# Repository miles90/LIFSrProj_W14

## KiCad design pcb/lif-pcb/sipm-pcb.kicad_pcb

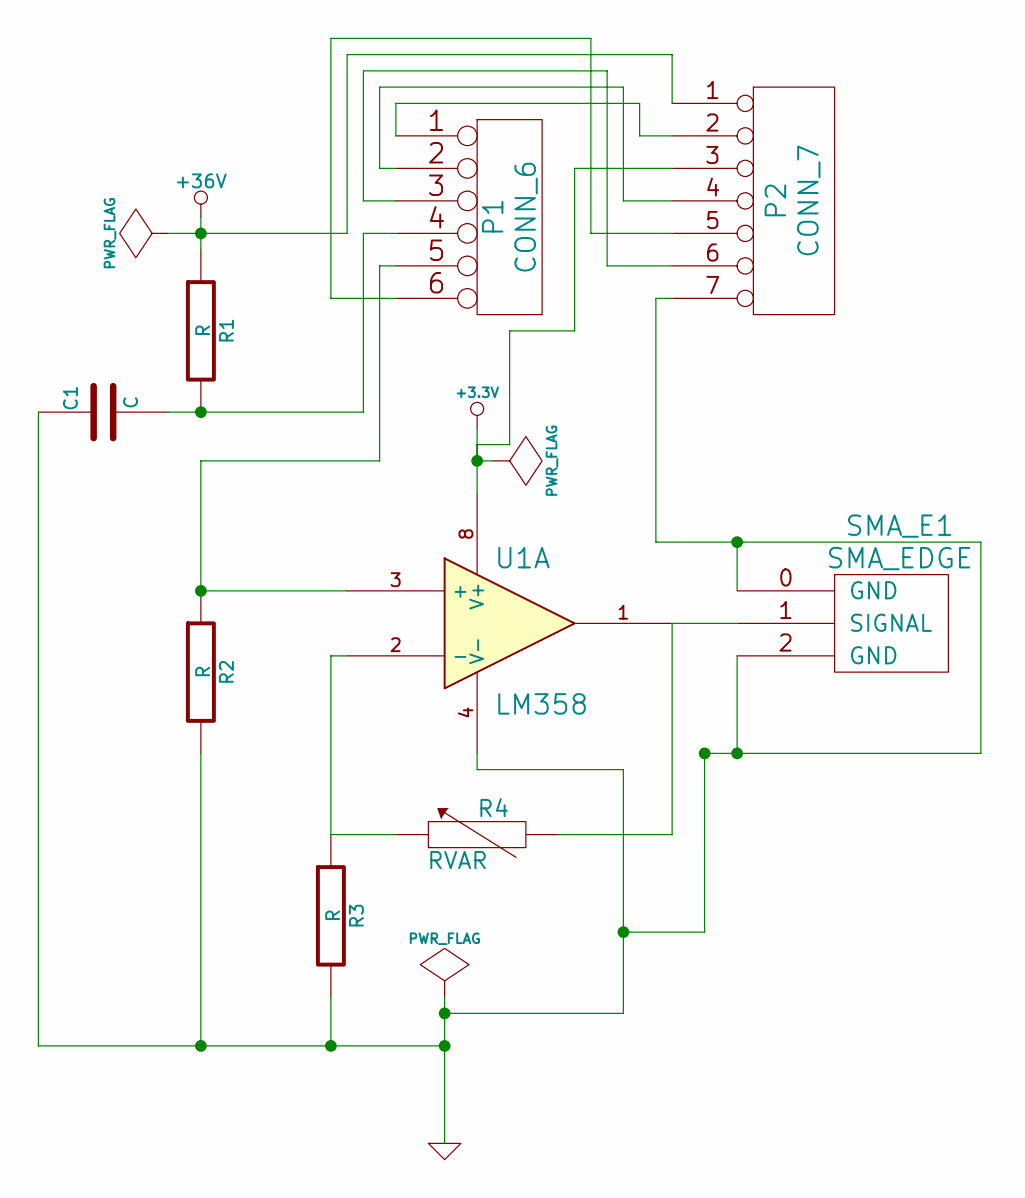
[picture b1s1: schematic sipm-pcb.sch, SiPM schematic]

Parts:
C1: C
P1: CONN_6
P2: CONN_7
R1, R2, R3: R
R4: RVAR
SMA_E1: SMA_EDGE
U1: LM358

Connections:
+3.3V: P2.3, U1.8 (V+)
+36V: P2.1, R1.1
GND: C1.1, P2.7, R2.2, R3.2, SMA_E1.0 (GND), SMA_E1.2 (GND), U1.4 (V-)
unnamed: P1.1, P2.2
unnamed: P1.5, R2.1, U1.3 (+)
unnamed: P1.6, P2.5
unnamed: P1.3, P2.6
unnamed: P1.2, P2.4
unnamed: C1.2, P1.4, R1.2
unnamed: R3.1, R4.1, U1.2 (-)
unnamed: R4.2, SMA_E1.1 (SIGNAL), U1.1

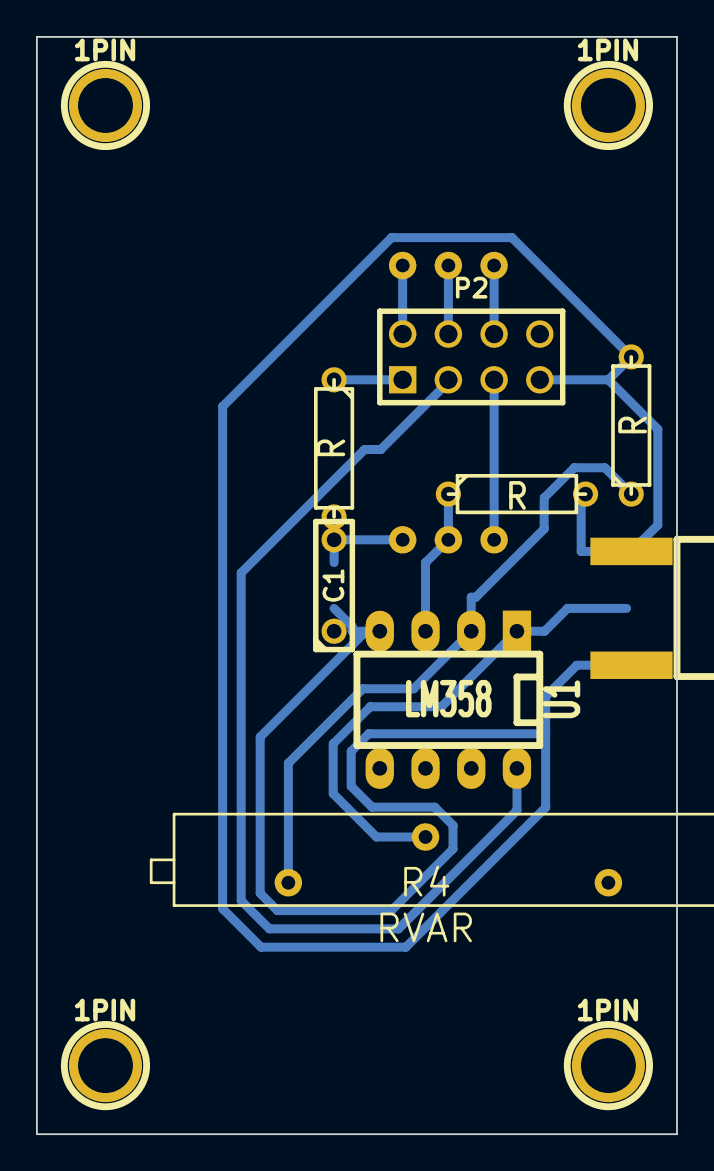
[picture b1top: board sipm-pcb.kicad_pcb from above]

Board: 2 copper layers, 35.6 x 61.0 mm, 13 parts (1 on the bottom side), 11 nets.

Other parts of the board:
1PIN, 1PIN#2, 1PIN#3, 1PIN#4: P***; 1pin

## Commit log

2014-03-12 Test commit - Chris's model
2014-03-13 Added my scads to the repo
2014-03-13 added stl
2014-03-19 Moved and added scads
2014-03-19 Added Translation stages
    Added Pinhole, sample slide and components. I need to break up the
    stages into modular components to print and polish off the pieces to the
    right sizes
2014-03-19 changed slide translation stage 2
    Put the slide tray between the tbs and linear bearing
2014-03-19 Added Threadless ball screws
    tbs with mount attachments and variable adjustment
2014-03-20 adding mounting holes to fluidic slide stage
    adding mounting holes to fluidic slide stage
2014-03-21 Finished slide sample stage
    Added adjustable components to tighten pieces together. Added stl files
2014-03-21 Changed tbs to smaller flex cut
2014-03-25 Broke the outer axis mounts into 2 pieces
2014-03-27 Started shrinking the pinhole stage
2014-03-27 Z axis model for stage
    I think...
2014-03-28 added LED light tube model for calibrating SiPM
2014-03-28 added pid code
2014-03-29 teensy changes to do pid once per ms
2014-03-31 Adding to repo
    Still waiting on print
2014-03-31 Added frame mounts
2014-03-31 shrinking pinhole
2014-03-31 added kicad files for SiPM
2014-03-31 added sipm moduel to the teensy module
2014-04-01 Fixed sample_lin_bearing
2014-04-01 Shrinking pinhole stage
    Because we have seen issues with the guide shaft not moving with the
    drive shaft when the two are not close together, I moved the two shafts
    to be as close as they can be together
2014-04-01 making version 2 of sample stage
2014-04-02 Changing drive mounts to guide mounts
2014-04-02 SiPM Light readings -- not good
2014-04-02 Added third outer profile stage
    Added a cross beam that will connect the two outer guiding rods. Need to
    add tbs with connections and then a motor mount and a rotating stop
    mount
2014-04-02 Added tbs mount for outer axis drive shaft
2014-04-02 Unknown? Does this belong to anybody?
    I'm not sure whose working on the Tubes library but I went ahead and
    committed it. CM
2014-04-03 Finished second iteration of sample translation
2014-04-03 Lengthened outer bearing mount
    Lengthened the arm to the outer bearing mount and shortened the distance
    the outer axis drive shaft would have to reach so that we can use the
    current cuts of rods.
2014-04-07 optical stage mount
    I'm fairly certain the model should be printable now.
2014-04-07 motor code
2014-04-08 finalizing trans stages
2014-04-09 shrunk base for printing
2014-04-09 unimportant change
2014-04-09 added platform to pinhole
2014-04-09 more motor code
2014-04-10 motor code change
2014-04-10 test
2014-04-10 optical stage base mount
2014-04-16 Added Awesomeness. Really
2014-04-16 The awesomest version of the processing gui yet
